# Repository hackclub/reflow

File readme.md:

# Reflow!

It's a YSWS. You ship something, we ship something to you in return. Run by gh@pmnlla

## Phase 1: Submit a design!

**You ship:** A printed circuit board.

- Your full design criteria is situated at [the website](https://reflow.hackclub.com). Have a look through it, you'll need it later :3
- Your folder structure should look just about like this:
```   
    - pcb                          
       └──name of your pcb                                                                                    
         ├────────README.md                                                 
         └────────cad                                                   
                   ├──────<name>.kicad_sch                              
                   ├──────<name>.kicad_pcb                             
                   ├──────<name>.kicad_dru                          
                   └──────<name>.kicad_pro     

```
  Send it over in a PR, we'll review it, and dispatch the WS prize!
- A series of files you are not allowed to upload:
  - Anything with wildcards, relative paths, or attempts to escape your submission in the /pcb directory
  - PCB files that do NOT pass DRC with 0 errors.
  - Edits to folders you have not made the previous commit to, i.e. folders that are not your PCB.
  - Backups, ZIPs, or entire component libraries. There should be a link to where to find them in your README.
  - Gerbers - unlike onboard, this YSWS generates gerbers per every submission, for manual reviewl You do not need to upload them, and it is discouraged.

Got questions? You can reach me on slack @ `U078HNSV750`

**We ship:** A practice kit to learn SMD soldering with!

You'll get a:
- Practice board, with a set functionality of a 7 segment counter. 4 of them, to be exact.
- Components to populate at least one of the boards with
- A pair of tweezers
- A tub of flux
- A tin of solder paste, low melt, unleaded.
- A USB-C powered hotplate!

## Phase 2: Learn to solder:

**You ship:** Evidence of a completed and functional practice board, to the smallest components you can see and solder.
**We ship:** Funds, through HCB, for you to get your very own design made, and get the parts to assemble it with!

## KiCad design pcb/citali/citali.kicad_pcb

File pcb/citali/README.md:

# citali

Currently, just a test PCB for me to check whether the auto review workflow actually, well, reviews.

Soon, an rp2040 devboard, eventually.

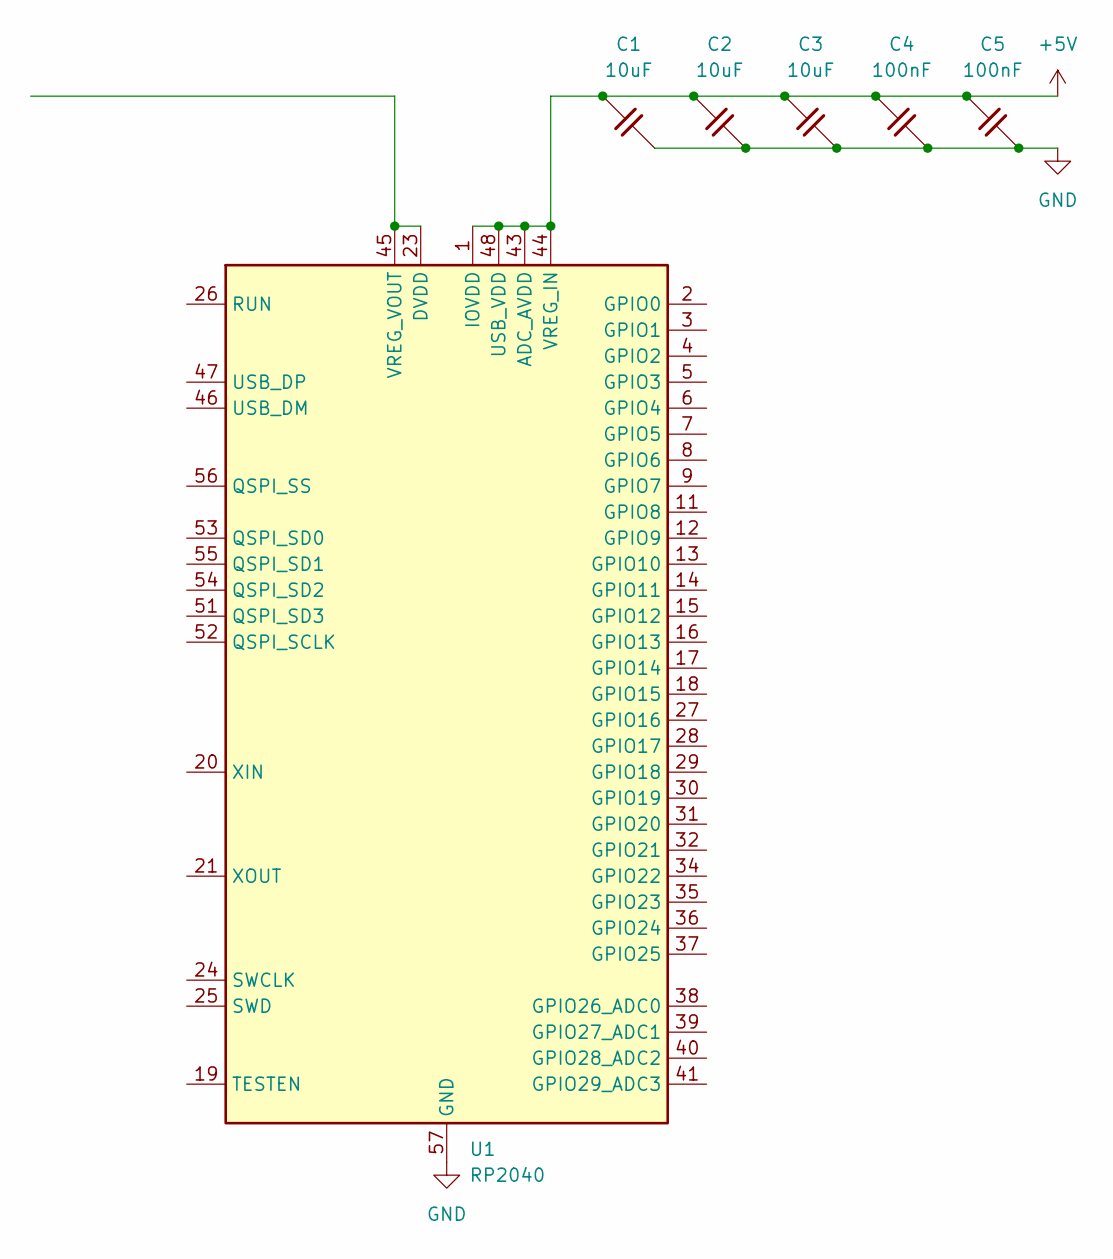
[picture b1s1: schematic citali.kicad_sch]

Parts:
C1, C2, C3: 10uF; C_0402_1005Metric
C4, C5: 100nF; C_0402_1005Metric
U1: RP2040; QFN-56-1EP_7x7mm_P0.4mm_EP3.2x3.2mm

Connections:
+5V: C1.2, C2.2, C3.2, C4.2, C5.2, U1.1 (IOVDD), U1.10 (IOVDD), U1.22 (IOVDD), U1.33 (IOVDD), U1.42 (IOVDD), U1.43 (ADC_AVDD), U1.44 (VREG_IN), U1.48 (USB_VDD), U1.49 (IOVDD)
GND: C1.1, C2.1, C3.1, C4.1, C5.1, U1.57 (GND)
unnamed: U1.23 (DVDD), U1.45 (VREG_VOUT), U1.50 (DVDD)

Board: 2 copper layers, 6 parts (0 on the bottom side), 3 nets, no tracks yet.

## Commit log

2025-07-08 biiiiiiiiig stretch! (pr workflow update: introduce tasks)
2025-07-08 almost forgot to upload artifacts!
2025-07-08 Add gerber generation task!
2025-07-08 statically define some stuff for extra hackatime minutes :3
2025-07-14 add github comment posting ritual
2025-07-14 add faulty test pcb
2025-07-15 Add debug terminal to workflow
2025-07-15 Add debug terminal switch
2025-07-15 I give up trying to get this workflow to debug itself so i'm forcing a debug terminal.
2025-07-15 forgot to force the terminal ugh
2025-07-15 found the bug! disable the terminal, time to squash!
2025-07-15 squash bug: python subprocess treats shell=true on windows, but shell=false on *nix. Force shell=true.
2025-07-15 Oh yeah, enable drill files too, why not?
2025-07-15 Disable manual toggle for terminal & manual launch action. Reserve this pipeline for PRs editing kicad files.
2025-07-21 Swap the action to the BorderCollei account
2025-07-28 Create FAULTY
2025-07-28 Update check-pcb-drc.yml
    This commit accomplishes full "immutability" of the workflow files in the sense that:
    - Python-based pipeline intents ensure the commit does not escape the /pcb/ directory
    - When opening a PR, the workflow that is registered to it originates from the trunk branch, not the commit branch.
    - The workflow restores _only_ the PCB directory from the commit branch during tests
2025-07-28 Update GenerateGerbers.py - Kicad does not actually have a --format flag for plotting
2025-08-08 Added a couple of things, notably better logging (and finally, runlevels!)
2025-08-08 Add CODEOWNERS
